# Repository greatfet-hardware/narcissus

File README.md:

# Narcissus
a GreatFET neighbor that is a jig for testing Azalea

Required KiCad dependency:

https://github.com/greatscottgadgets/gsg-kicad-lib

If you are using git, the preferred way to install gsg-kicad-lib is to use the
submodule:

```
git submodule init && git submodule update
```

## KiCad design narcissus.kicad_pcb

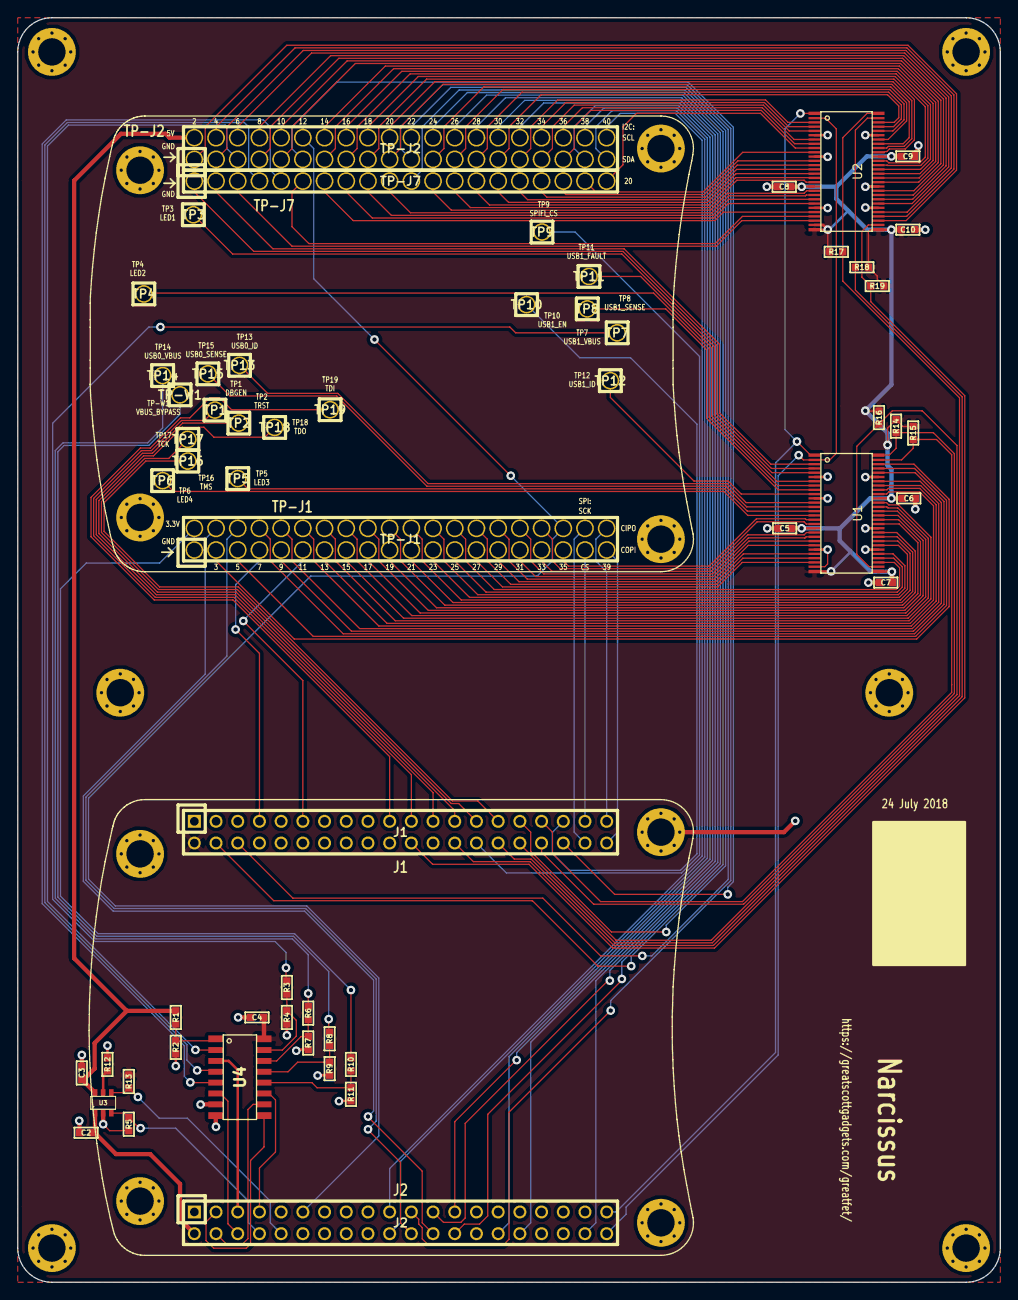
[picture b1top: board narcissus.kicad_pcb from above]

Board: 2 copper layers, 115.0 x 148.0 mm, 71 parts (0 on the bottom side), 142 nets.

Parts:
C2, C3: 1µF; 0603
C4, C5, C6, C7, C8, C9, C10: 100nF; 0603
J1: NEIGHBOR1; HEADER-2x20-REVERSE
J2: NEIGHBOR2; HEADER-2x20-REVERSE
MH1, MH2, MH3, MH4, MH5, MH6, MH7, MH8, MH9, MH10, MH11, MH12, MH13, MH14: MOUNTING_HOLE; HOLE126MIL-COPPER
R1, R2, R3, R4, R5, R6, R7, R8, R9, R10, R11, R13, R14, R15, R16, R17, R18, R19: 12.0k; 0603
R12: 43.2k; 0603
TP1: DBGEN; HEADER-1x1-TESTPROBE
TP2: TRST; HEADER-1x1-TESTPROBE
TP3: LED1; HEADER-1x1-TESTPROBE
TP4: LED2; HEADER-1x1-TESTPROBE
TP5: LED3; HEADER-1x1-TESTPROBE
TP6: LED4; HEADER-1x1-TESTPROBE
TP7: USB1_VBUS; HEADER-1x1-TESTPROBE
TP8: USB1_SENSE; HEADER-1x1-TESTPROBE
TP9: SPIFI_CS; HEADER-1x1-TESTPROBE
TP10: USB1_EN; HEADER-1x1-TESTPROBE
TP11: USB1_FAULT; HEADER-1x1-TESTPROBE
TP12: USB1_ID; HEADER-1x1-TESTPROBE
TP13: USB0_ID; HEADER-1x1-TESTPROBE
TP14: USB0_VBUS; HEADER-1x1-TESTPROBE
TP15: USB0_SENSE; HEADER-1x1-TESTPROBE
TP16: TMS; HEADER-1x1-TESTPROBE
TP17: TCK; HEADER-1x1-TESTPROBE
TP18: TDO; HEADER-1x1-TESTPROBE
TP19: TDI; HEADER-1x1-TESTPROBE
TP-J1: EUT_NEIGHBOR1; HEADER-2x20-TESTPROBE
TP-J2: EUT_NEIGHBOR2; HEADER-2x20-TESTPROBE
TP-J7: EUT_BONUS_ROW; HEADER-1x20-TESTPROBE
TP-W1: VBUS_BYPASS; HEADER-1x1-TESTPROBE
U1, U2: PCA9698; TSSOP56
U3: AP2553W6-7; SOT457
U4: 74HC4051; SOIC16

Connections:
+5V: C2.1, J2.2, U3.1
/ADC0_0: J2.5, U4.3
/CLK0: J1.11, TP-J1.11
/EUT_5V: C3.1, R1.1, TP-J2.2, U3.6
/EUT_ADC0_0: TP-J2.5, U4.2
/EUT_ADC0_2: TP-J7.5, U4.5
/EUT_ADC0_5: TP-J7.4, U4.4
/EUT_VCC: R10.1, TP-J1.2
/I2C0_SCL: J2.40, U1.2, U2.2
/I2C0_SDA: J2.39, U1.1, U2.1
/P0_0: J1.4, TP-J2.24
/P0_1: J1.6, TP-J2.22
/P1_0: J1.7, TP-J1.7
/P1_3: J1.40, TP-J1.39
/P1_4: J1.39, TP-J1.40
/P1_11: J1.22, R19.2, U2.30
/P1_12: J1.21, TP1.1
/P1_13: J1.26, R18.2, U2.55
/P1_14: J1.25, TP18.1
/P1_15: J1.28, TP9.1
/P1_16: J1.30, R17.2, U2.56
/P1_17: J1.32, R16.2, U1.30
/P1_18: J1.31, TP-J7.11
/P1_19: J1.38, TP-J1.38
/P1_20: J1.37, TP-J1.37
/P2_0: J1.35, TP10.1
/P2_3: J2.20, TP-J2.39
/P2_4: J2.19, TP-J2.40
/P3_0: J2.26, TP-J2.26
/P3_1: J2.24, TP-J1.4
/P3_2: J2.22, TP-J1.6
/P3_3: J2.32, TP-J2.32
/P3_6: J2.38, TP-J2.30
/P3_7: J2.30, TP-J2.38
/P4_0: J2.4, U4.10
/P4_2: J2.8, R5.1, U3.3
/P4_4: J2.7, U4.11
/P4_5: J2.6, U4.6
/P4_6: J2.10, R13.2, U3.4
/P4_7: J2.11, TP-J1.36, TP-J2.12
/P4_8: J2.3, U4.9
/P5_3: J1.19, TP19.1
/P5_5: J1.23, TP2.1
/P5_6: J1.27, TP17.1
/P5_7: J1.29, TP16.1
/P6_0: J1.36, TP-J2.11
/P7_1: J2.25, TP-J2.37
/P7_2: J2.23, TP-J2.28
/P9_5: J1.33, R15.2, U1.55
/P9_6: J1.34, R14.2, U1.56
/PF_4: J2.21, TP-J2.21
/U1_IO0_0: TP-J7.2, U1.3
/U1_IO0_1: TP-J7.1, U1.4
/U1_IO0_2: TP3.1, U1.5
/U1_IO0_3: TP11.1, U1.7
/U1_IO0_4: TP4.1, U1.8
/U1_IO0_5: TP8.1, U1.9
/U1_IO0_6: TP12.1, U1.10
/U1_IO0_7: TP13.1, U1.12
/U1_IO1_0: TP15.1, U1.13
/U1_IO1_1: TP5.1, U1.14
/U1_IO1_2: TP6.1, U1.15
/U1_IO1_3: TP-J1.35, U1.16
/U1_IO1_4: TP-J1.34, U1.17
/U1_IO1_5: TP-J1.33, U1.19
/U1_IO1_6: TP-J1.32, U1.20
/U1_IO1_7: TP-J1.31, U1.21
/U1_IO2_0: TP-J1.30, U1.22
/U1_IO2_1: TP-J1.29, U1.24
/U1_IO2_2: TP-J1.28, U1.25
/U1_IO2_3: TP-J1.27, U1.26
/U1_IO2_4: TP-J1.26, U1.31
/U1_IO2_5: TP-J1.25, U1.32
/U1_IO2_6: TP-J1.24, U1.33
/U1_IO2_7: TP-J1.23, U1.35
/U1_IO3_0: TP-J1.22, U1.36
/U1_IO3_1: TP-J1.21, U1.37
/U1_IO3_2: TP-J1.20, U1.38
/U1_IO3_3: TP-J1.19, U1.40
/U1_IO3_4: TP-J1.18, U1.41
/U1_IO3_5: TP-J1.17, U1.42
/U1_IO3_6: TP-J1.16, U1.43
/U1_IO3_7: TP-J1.15, U1.44
/U1_IO4_0: TP-J1.14, U1.45
/U1_IO4_1: TP-J1.13, U1.47
/U1_IO4_2: TP-J1.12, U1.48
/U1_IO4_3: TP-J1.10, U1.49
/U1_IO4_4: TP-J1.9, U1.50
/U1_IO4_5: TP-J1.8, U1.52
/U1_IO4_6: TP-J1.5, U1.53
/U1_IO4_7: TP-J1.3, U1.54
/U2_IO0_0: TP-J2.31, U2.3
/U2_IO0_1: TP-J2.34, U2.4
/U2_IO0_2: TP-J2.33, U2.5
/U2_IO0_3: TP-J2.36, U2.7
/U2_IO0_4: TP-J2.35, U2.8
/U2_IO0_5: TP-J7.20, U2.9
/U2_IO0_6: TP-J7.19, U2.10
/U2_IO0_7: TP-J7.18, U2.12
/U2_IO1_0: TP-J7.17, U2.13
/U2_IO1_1: TP-J7.16, U2.14
/U2_IO1_2: TP-J7.15, U2.15
/U2_IO1_3: TP-J7.14, U2.16
/U2_IO1_4: TP-J7.13, U2.17
/U2_IO1_5: TP-J7.12, U2.19
/U2_IO1_6: TP-J7.10, U2.20
/U2_IO1_7: TP-J7.9, U2.21
/U2_IO2_0: TP-J7.8, U2.22
/U2_IO2_1: TP-J7.7, U2.24
/U2_IO2_2: TP-J7.6, U2.25
/U2_IO2_3: TP-J7.3, U2.26
/U2_IO2_4: TP-J2.1, U2.31
/U2_IO2_5: TP-J2.4, U2.32
/U2_IO2_6: TP-J2.3, U2.33
/U2_IO2_7: TP-J2.6, U2.35
/U2_IO3_0: TP-J2.8, U2.36
/U2_IO3_1: TP-J2.7, U2.37
/U2_IO3_2: TP-J2.10, U2.38
/U2_IO3_3: TP-J2.9, U2.40
/U2_IO3_4: TP-J2.14, U2.41
/U2_IO3_5: TP-J2.13, U2.42
/U2_IO3_6: TP-J2.16, U2.43
/U2_IO3_7: TP-J2.15, U2.44
/U2_IO4_0: TP-J2.18, U2.45
/U2_IO4_1: TP-J2.17, U2.47
/U2_IO4_2: TP-J2.20, U2.48
/U2_IO4_3: TP-J2.19, U2.49
/U2_IO4_4: TP-J2.23, U2.50
/U2_IO4_5: TP-J2.25, U2.52
/U2_IO4_6: TP-J2.27, U2.53
/U2_IO4_7: TP-J2.29, U2.54
GND: C2.2, C3.2, C4.2, C5.2, C6.2, C7.2, C8.2, C9.2, C10.2, J1.1, J2.1, MH1.1, MH2.1, MH3.1, MH4.1, R2.2, R4.2, R5.2, R7.2, R9.2, R11.2, R12.2, TP-J1.1, U1.6, U1.11, U1.23, U1.27, U1.34, U1.39, U1.51, U2.6, U2.11, U2.23, U2.34, U2.39, U2.51, U3.2, U4.7, U4.8
unnamed: R1.2, R2.1, U4.1
unnamed: R3.1, TP7.1
unnamed: R3.2, R4.1, U4.15
unnamed: R6.1, TP14.1
unnamed: R6.2, R7.1, U4.14
unnamed: R8.1, TP-W1.1
unnamed: R8.2, R9.1, U4.13
unnamed: R10.2, R11.1, U4.12
unnamed: R12.1, U3.5
VCC: C4.1, C5.1, C6.1, C7.1, C8.1, C9.1, C10.1, J1.2, R13.1, R14.1, R15.1, R16.1, R17.1, R18.1, R19.1, U1.18, U1.28, U1.29, U1.46, U2.18, U2.27, U2.28, U2.29, U2.46, U4.16

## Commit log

2019-05-27 split narcissus into separate repository
2019-05-27 updated README.md to be narcissus-specific
2020-07-03 adopt OSHWA convention for SPI signal names https://www.oshwa.org/a-resolution-to-redefine-spi-signal-names

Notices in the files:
narcissus.kicad_pcb:
Copyright 2018 Great Scott Gadgets
License: BSD-3-Clause
